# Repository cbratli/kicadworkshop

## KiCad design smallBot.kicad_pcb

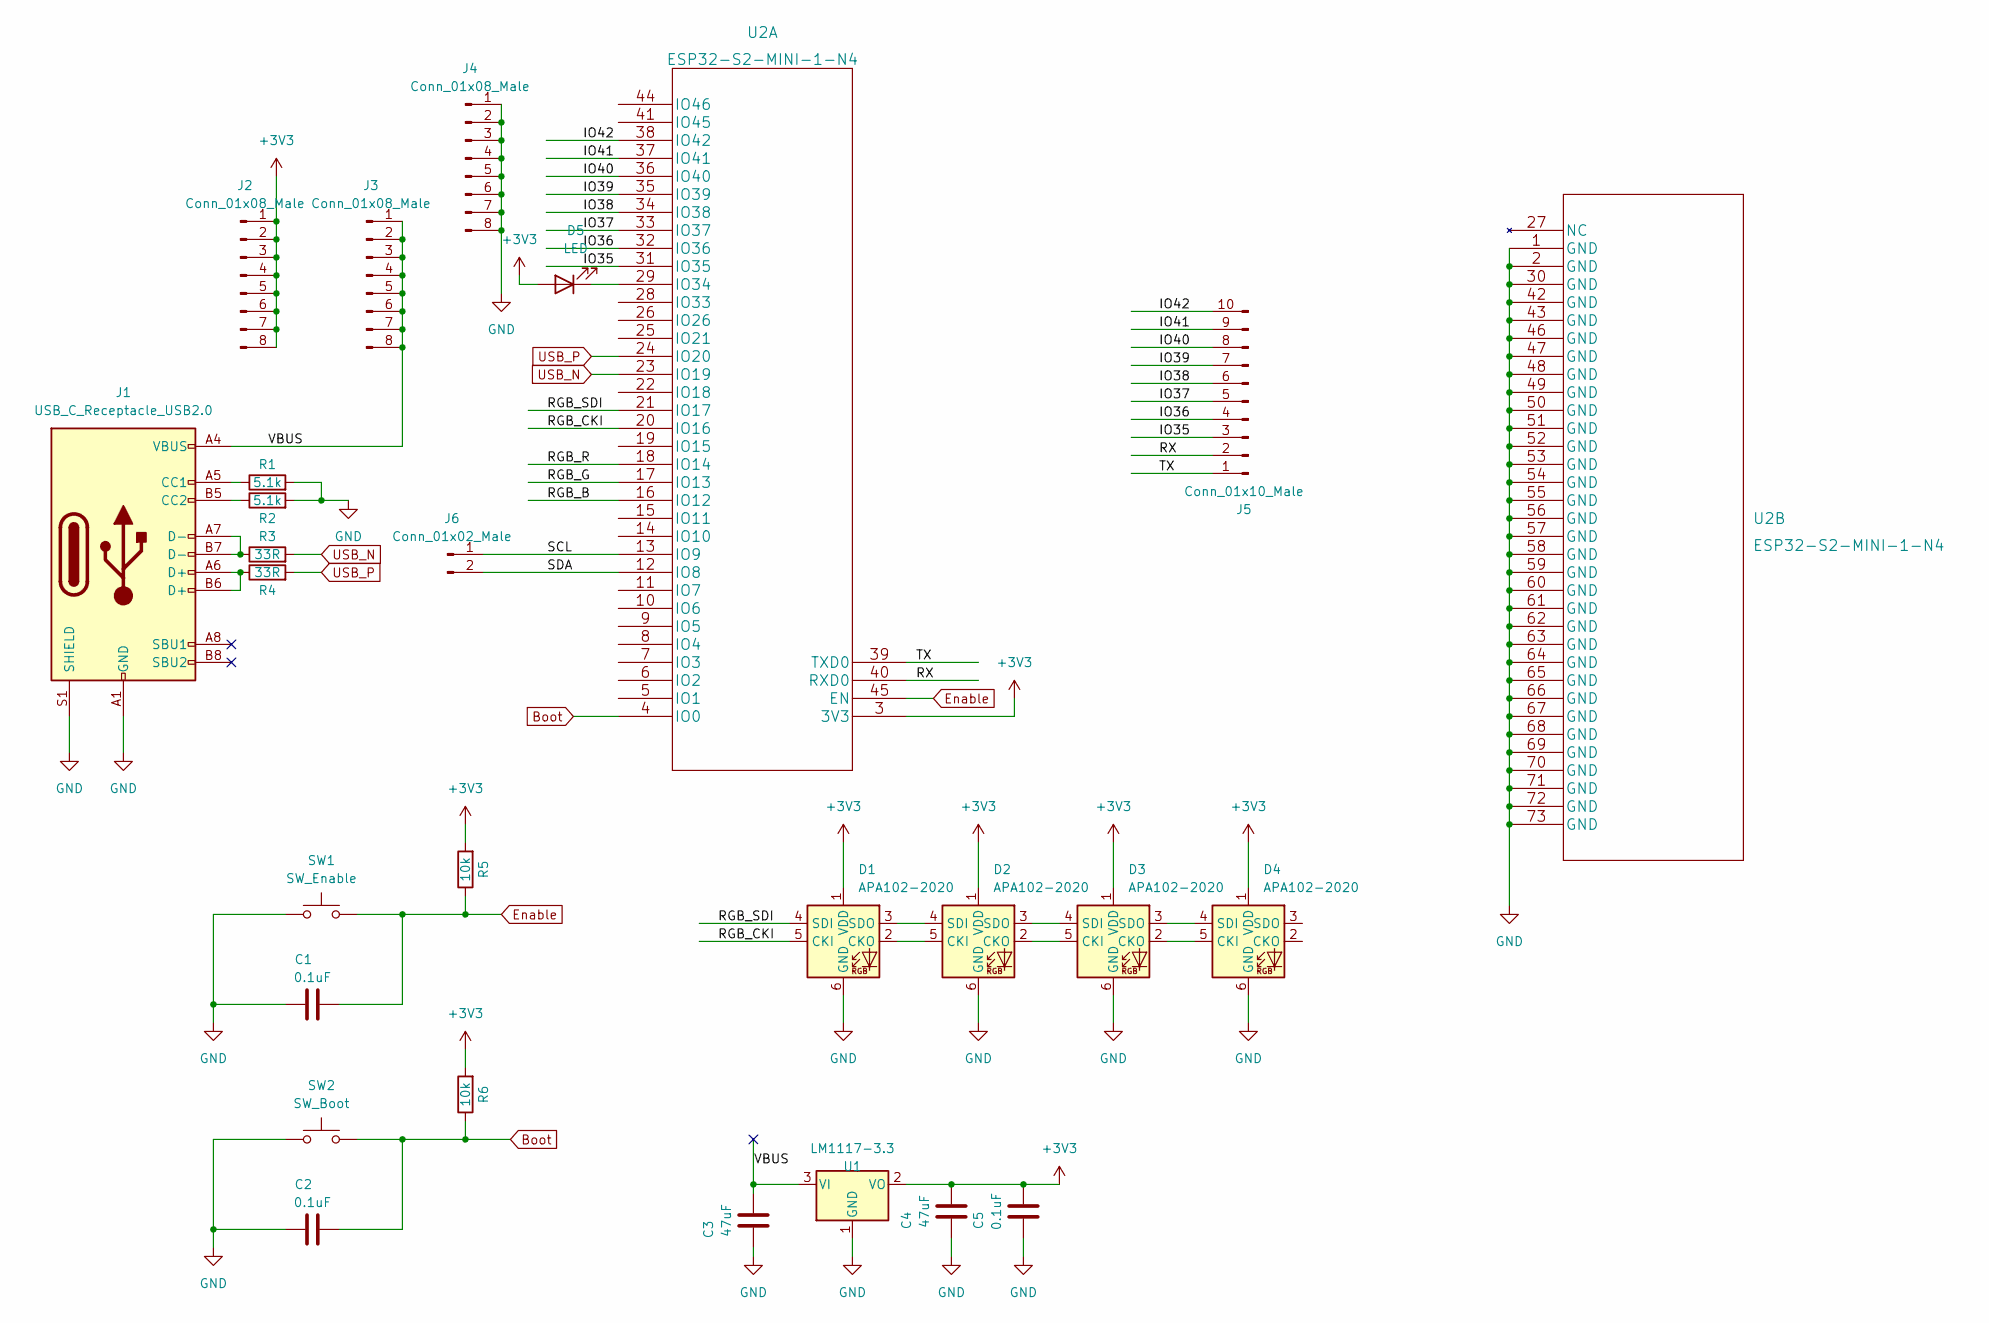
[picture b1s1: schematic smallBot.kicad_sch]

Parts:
C1, C2, C5: 0.1uF; C_0603_1608Metric
C3, C4: 47uF; C_0805_2012Metric
D1, D2, D3, D4: APA102-2020; LED-APA102-2020
D5: LED; LED_0603_1608Metric
J1: USB_C_Receptacle_USB2.0; TYPE-C-31-M-12
J2, J3, J4: Conn_01x08_Male; PinHeader_1x08_P2.54mm_Vertical
J5: Conn_01x10_Male; PinHeader_1x10_P2.54mm_Vertical
J6: Conn_01x02_Male; PinHeader_1x02_P2.54mm_Vertical
R1, R2: 5.1k; R_0603_1608Metric
R3, R4: 33R; R_0603_1608Metric
R5, R6: 10k; R_0603_1608Metric
SW1: SW_Enable; SW_SPST_Panasonic_EVQPL_3PL_5PL_PT_A08
SW2: SW_Boot; SW_SPST_Panasonic_EVQPL_3PL_5PL_PT_A08
U1: LM1117-3.3; SOT-223
U2: ESP32-S2-MINI-1-N4

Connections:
+3V3: C4.2, C5.2, D1.1 (VDD), D2.1 (VDD), D3.1 (VDD), D4.1 (VDD), D5.2 (A), J2.1, J2.2, J2.3, J2.4, J2.5, J2.6, J2.7, J2.8, R5.2, R6.2, U1.2 (VO), U2.3 (3V3)
/IO35: J5.3, U2.31 (IO35)
/IO36: J5.4, U2.32 (IO36)
/IO37: J5.5, U2.33 (IO37)
/IO38: J5.6, U2.34 (IO38)
/IO39: J5.7, U2.35 (IO39)
/IO40: J5.8, U2.36 (IO40)
/IO41: J5.9, U2.37 (IO41)
/IO42: J5.10, U2.38 (IO42)
/RGB_B: U2.16 (IO12)
/RGB_CKI: D1.5 (CKI), U2.20 (IO16)
/RGB_G: U2.17 (IO13)
/RGB_R: U2.18 (IO14)
/RGB_SDI: D1.4 (SDI), U2.21 (IO17)
/RX: J5.2, U2.40 (RXD0)
/SCL: J6.1, U2.13 (IO9)
/SDA: J6.2, U2.12 (IO8)
/TX: J5.1, U2.39 (TXD0)
/VBUS: C3.2, J1.A4 (VBUS), J1.A9 (VBUS), J1.B4 (VBUS), J1.B9 (VBUS), J3.1, J3.2, J3.3, J3.4, J3.5, J3.6, J3.7, J3.8, U1.3 (VI)
Boot: C2.2, R6.1, SW2.2, U2.4 (IO0)
Enable: C1.2, R5.1, SW1.2, U2.45 (EN)
GND: C1.1, C2.1, C3.1, C4.1, C5.1, D1.6 (GND), D2.6 (GND), D3.6 (GND), D4.6 (GND), J1.A1 (GND), J1.A12 (GND), J1.B1 (GND), J1.B12 (GND), J1.S1 (SHIELD), J4.1, J4.2, J4.3, J4.4, J4.5, J4.6, J4.7, J4.8, R1.2, R2.2, SW1.1, SW2.1, U1.1 (GND), U2.1 (GND), U2.2 (GND), U2.30 (GND), U2.42 (GND), U2.43 (GND), U2.46 (GND), U2.47 (GND), U2.48 (GND), U2.49 (GND), U2.50 (GND), U2.51 (GND), U2.52 (GND), U2.53 (GND), U2.54 (GND), U2.55 (GND), U2.56 (GND), U2.57 (GND), U2.58 (GND), U2.59 (GND), U2.60 (GND), U2.61 (GND), U2.62 (GND), U2.63 (GND), U2.64 (GND), U2.65 (GND), U2.66 (GND), U2.67 (GND), U2.68 (GND), U2.69 (GND), U2.70 (GND), U2.71 (GND), U2.72 (GND), U2.73 (GND)
unnamed: D1.2 (CKO), D2.5 (CKI)
unnamed: D1.3 (SDO), D2.4 (SDI)
unnamed: D2.2 (CKO), D3.5 (CKI)
unnamed: D2.3 (SDO), D3.4 (SDI)
unnamed: D3.2 (CKO), D4.5 (CKI)
unnamed: D3.3 (SDO), D4.4 (SDI)
unnamed: J1.A5 (CC1), R1.1
unnamed: J1.A6 (D+), J1.B6 (D+), R4.1
unnamed: J1.A7 (D-), J1.B7 (D-), R3.1
unnamed: J1.B5 (CC2), R2.1
unnamed: D5.1 (K), U2.29 (IO34)
USB_N: R3.2, U2.23 (IO19)
USB_P: R4.2, U2.24 (IO20)

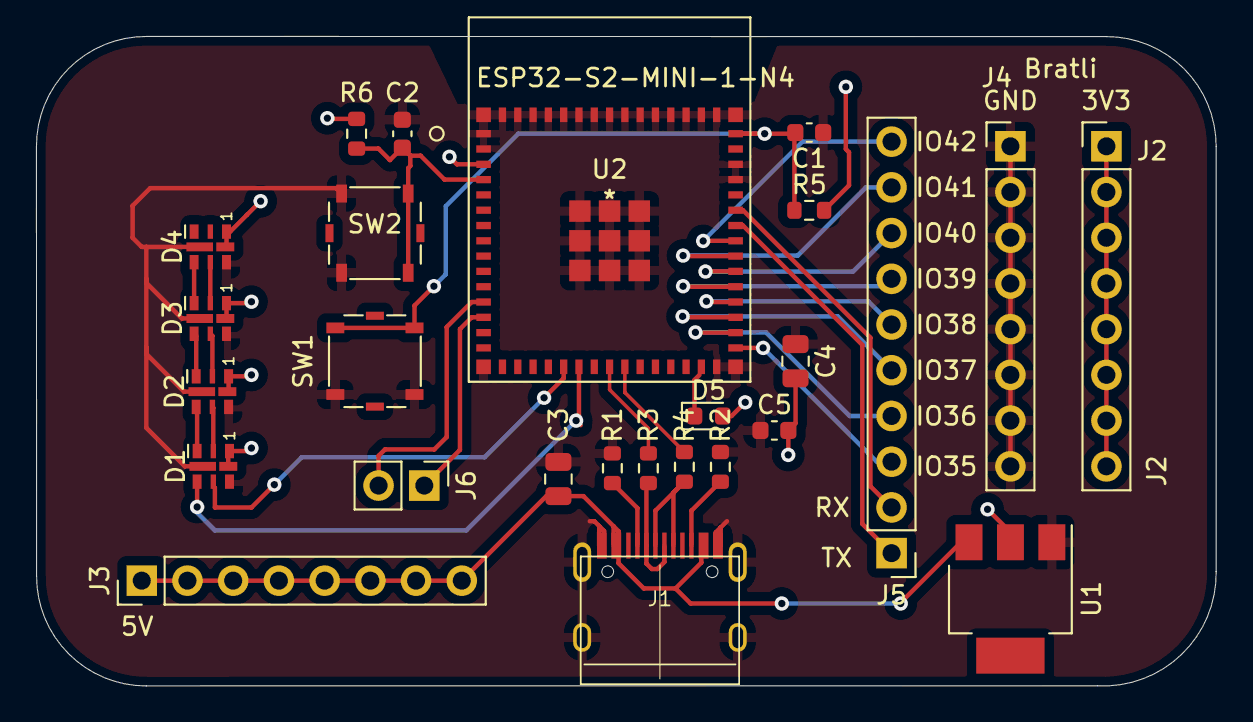
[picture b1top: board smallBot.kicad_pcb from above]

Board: 2 copper layers, 65.5 x 36.1 mm, 26 parts (0 on the bottom side), 32 nets.

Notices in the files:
parts and their libraries:
Copyright 2021 Accelerated Designs. All rights reserved.
